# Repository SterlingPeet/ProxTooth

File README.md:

ProxTooth
=========

This project involves the software and hardware required to read a HID prox card and make the card data available to a bluetooth client.

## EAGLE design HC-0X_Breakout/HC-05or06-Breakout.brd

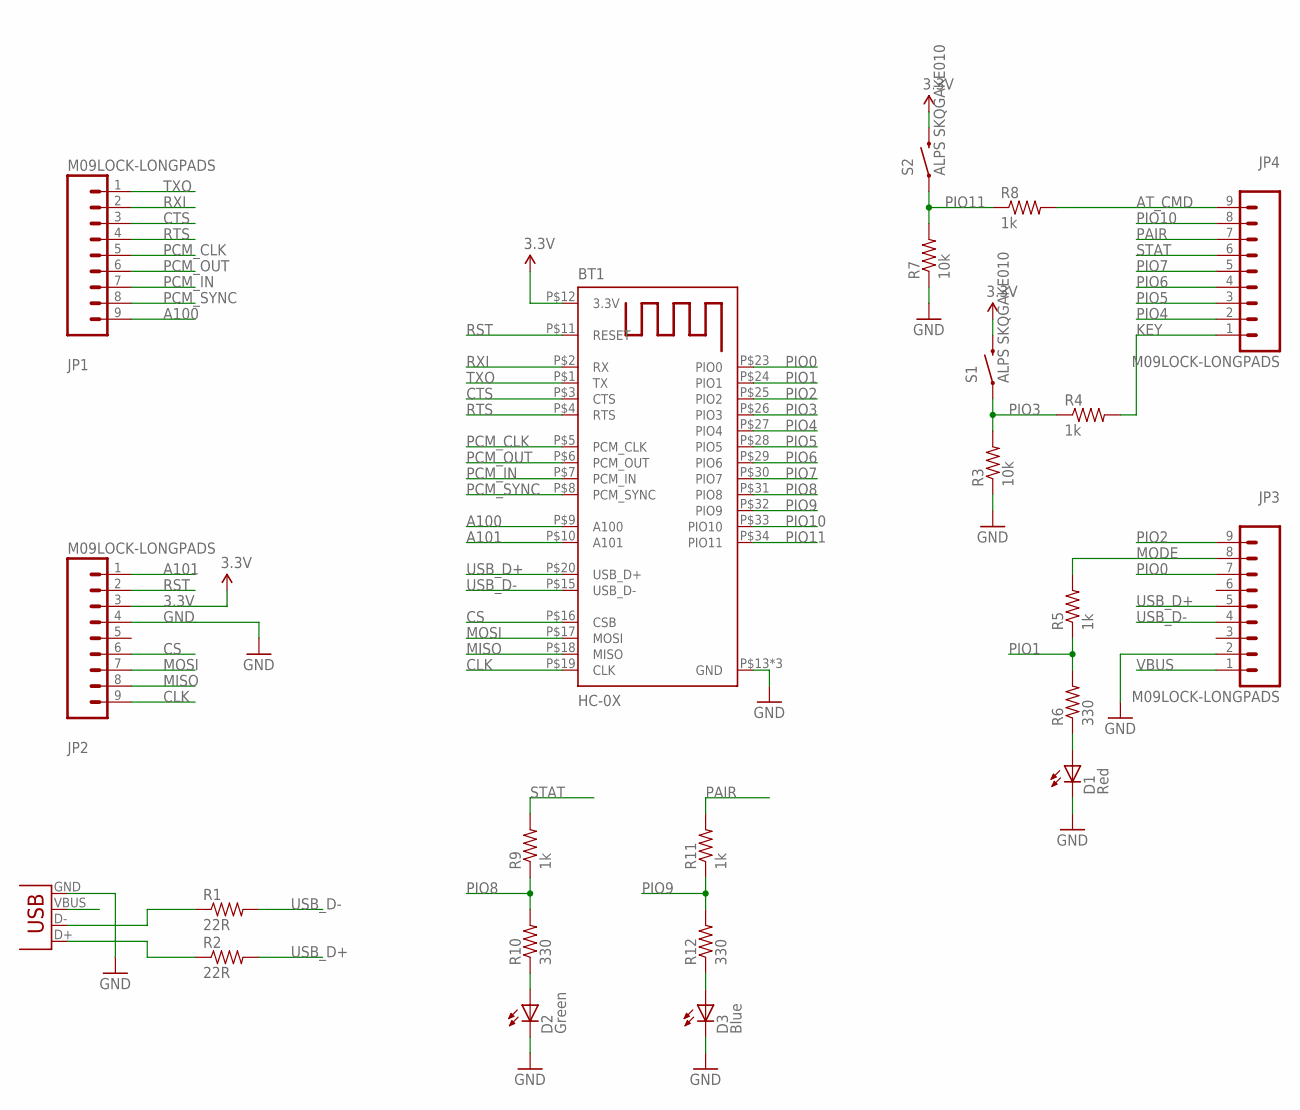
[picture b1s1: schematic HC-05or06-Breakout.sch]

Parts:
BT1: HC-0X
D1: Red; LED-0603
D2: Green; LED-0603
D3: Blue; LED-0603
JP1, JP2, JP3, JP4: M09LOCK-LONGPADS; 1X09_LOCK_LONGPADS
R1, R2: 22R; 0603-RES
R3, R7: 10k; 0603-RES
R4, R5, R8, R9, R11: 1k; 0603-RES
R6, R10, R12: 330; 0603-RES
S1, S2: ALPS SKQGAKE010; TACTILE_SWITCH_SMD
X1: USBSMD; USB-MINIB

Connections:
3.3V: BT1.P$12 (3.3V), JP2.3, S1.3 (2), S2.3 (2)
A100: BT1.P$9 (A100), JP1.9
A101: BT1.P$10 (A101), JP2.1
AT_CMD: JP4.9, R8.2
CLK: BT1.P$19 (CLK), JP2.9
CS: BT1.P$16 (CSB), JP2.6
CTS: BT1.P$3 (CTS), JP1.3
GND: BT1.P$13 (GND), BT1.P$21 (GND), BT1.P$22 (GND), D1.C, D2.C, D3.C, JP2.4, JP3.2, R3.1, R7.1, X1.GND
KEY: JP4.1, R4.2
MISO: BT1.P$18 (MISO), JP2.8
MODE: JP3.8, R5.2
MOSI: BT1.P$17 (MOSI), JP2.7
unnamed: D1.A, R6.1
unnamed: D2.A, R10.1
unnamed: D3.A, R12.1
unnamed: R1.1, X1.D-
unnamed: R2.1, X1.D+
PAIR: JP4.7, R11.2
PCM_CLK: BT1.P$5 (PCM_CLK), JP1.5
PCM_IN: BT1.P$7 (PCM_IN), JP1.7
PCM_OUT: BT1.P$6 (PCM_OUT), JP1.6
PCM_SYNC: BT1.P$8 (PCM_SYNC), JP1.8
PIO0: BT1.P$23 (PIO0), JP3.7
PIO1: BT1.P$24 (PIO1), R5.1, R6.2
PIO2: BT1.P$25 (PIO2), JP3.9
PIO3: BT1.P$26 (PIO3), R3.2, R4.1, S1.1
PIO4: BT1.P$27 (PIO4), JP4.2
PIO5: BT1.P$28 (PIO5), JP4.3
PIO6: BT1.P$29 (PIO6), JP4.4
PIO7: BT1.P$30 (PIO7), JP4.5
PIO8: BT1.P$31 (PIO8), R9.1, R10.2
PIO9: BT1.P$32 (PIO9), R11.1, R12.2
PIO10: BT1.P$33 (PIO10), JP4.8
PIO11: BT1.P$34 (PIO11), R7.2, R8.1, S2.1
RST: BT1.P$11 (RESET), JP2.2
RTS: BT1.P$4 (RTS), JP1.4
RXI: BT1.P$2 (RX), JP1.2
STAT: JP4.6, R9.2
TXO: BT1.P$1 (TX), JP1.1
USB_D+: BT1.P$20 (USB_D+), JP3.5, R2.2
USB_D-: BT1.P$15 (USB_D-), JP3.4, R1.2
VBUS: JP3.1, X1.VBUS

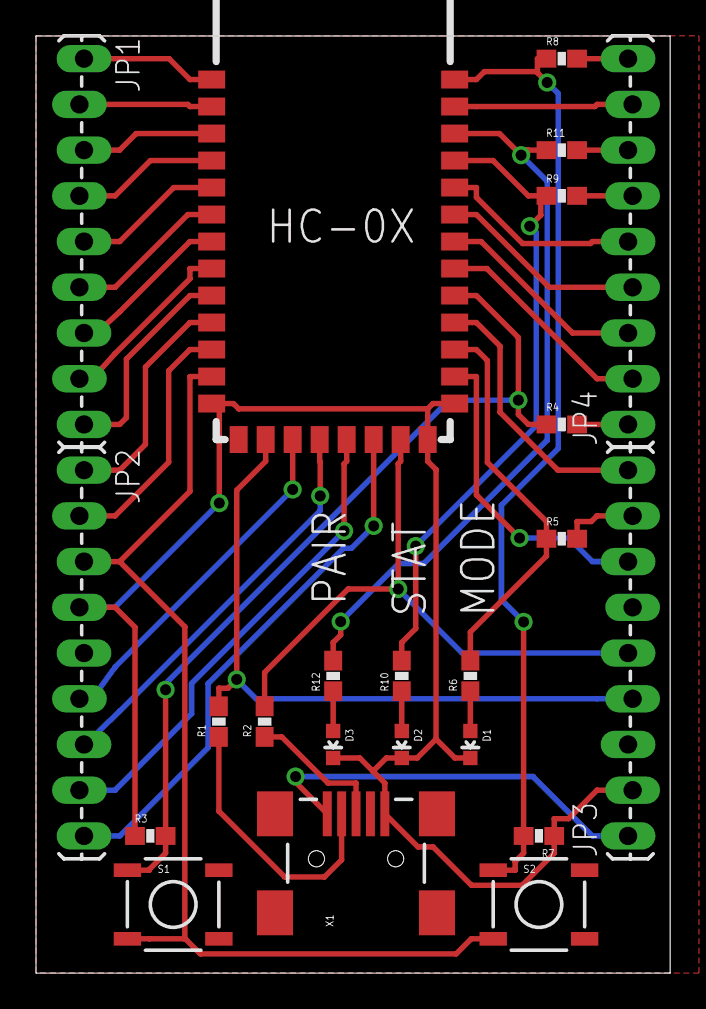
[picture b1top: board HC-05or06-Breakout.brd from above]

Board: 2 copper layers, 35.2 x 52.1 mm, 23 parts (0 on the bottom side), 42 nets.

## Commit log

2012-10-03 Finished breakout board and exported gerber files
2013-02-20 fix silkscreen alignment errors

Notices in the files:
parts and their libraries:
SparkFun-Connectors: Licensing: CC v3.0 Share-Alike You are welcome to use this library for commercial purposes.
